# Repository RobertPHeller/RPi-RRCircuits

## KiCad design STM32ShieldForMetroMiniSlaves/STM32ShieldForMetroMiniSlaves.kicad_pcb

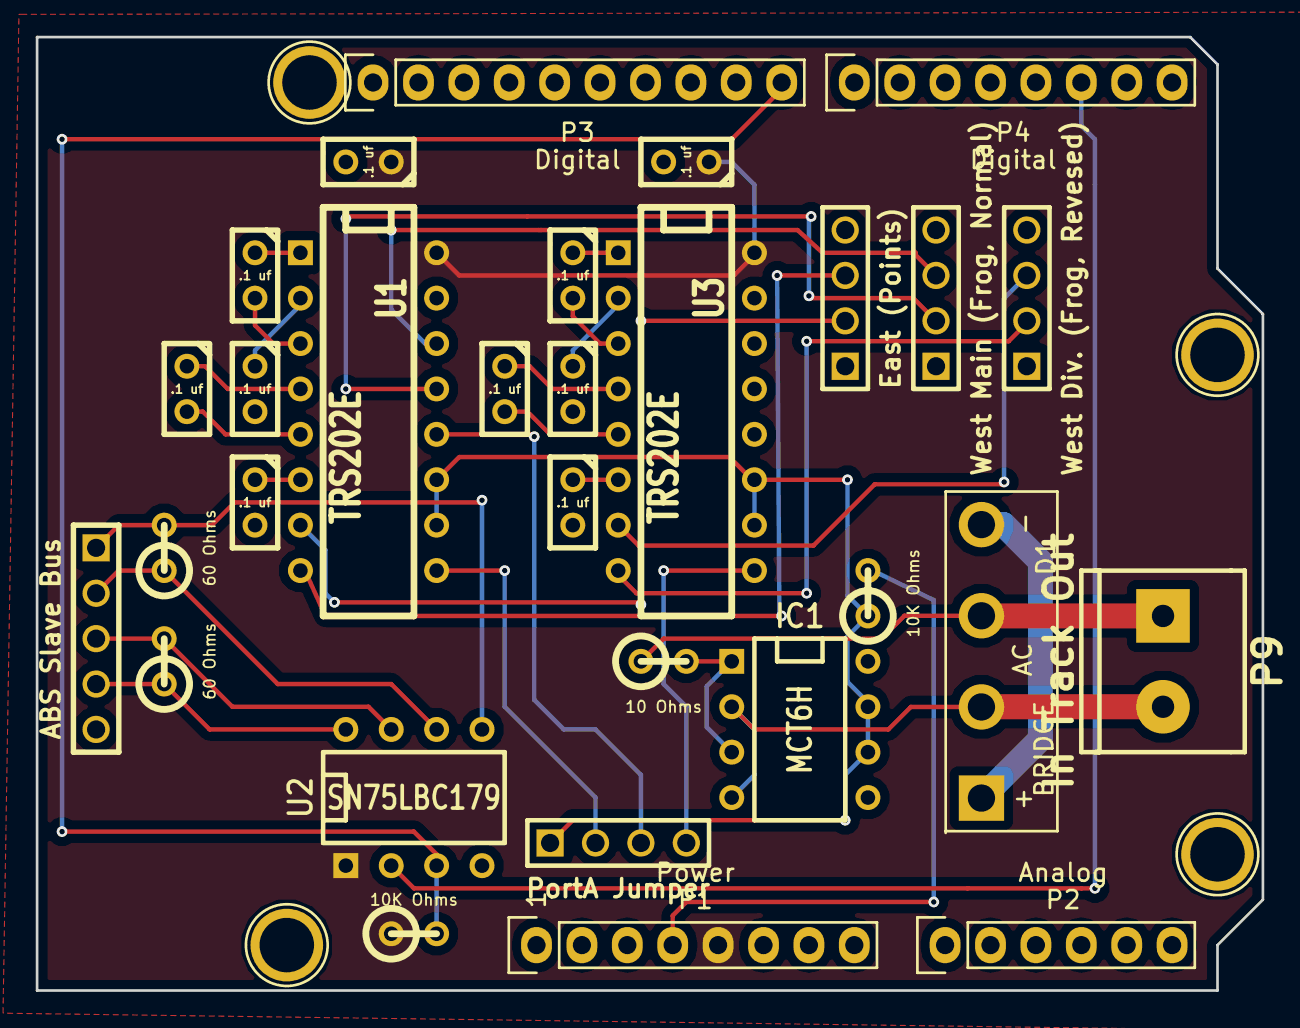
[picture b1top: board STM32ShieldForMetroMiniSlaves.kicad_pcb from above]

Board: 2 copper layers, 68.6 x 53.3 mm, 34 parts (0 on the bottom side), 35 nets.

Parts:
C1, C2, C3, C4, C5, C6, C7, C8, C9, C10: .1 uf; C1
D1: BRIDGE; KBL
IC1: MCT6H; DIP-8__300
P1: Power; Socket_Strip_Arduino_1x08
P2: Analog; Socket_Strip_Arduino_1x06
P3: Digital; Socket_Strip_Arduino_1x10
P4: Digital; Socket_Strip_Arduino_1x08
P5, P6, P7, P8: CONN_01X01; Arduino_1pin
P9: In Track Out; mors_2p
P10: East (Points); PIN_ARRAY_4x1
P11: West Main (Frog, Normal); PIN_ARRAY_4x1
P12: ABS Slave Bus; PIN_ARRAY_5x1
P13: West Div. (Frog, Revesed); PIN_ARRAY_4x1
P14: PortA Jumper; PIN_ARRAY_4x1
R1: 10 Ohms; R1
R2, R5: 10K Ohms; R1
R3, R4: 60 Ohms; R1
U1, U3: TRS202E; DIP-16__300
U2: SN75LBC179; DIP-8__300

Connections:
+3.3V: P1.4, R2.2
+5V: C5.1, C10.1, P1.5, R5.1, U1.16, U2.1, U3.16
/2: P4.6, U2.2
/8: P3.10, R5.2, U2.3
/PortA 5: IC1.6, IC1.7, P14.1, R2.1, U1.10, U1.11, U3.10, U3.11
/PortA 6: P14.2, U1.9
/PortA 7: P14.3, U1.12
/PortA 8: P14.4, U3.9
GND: C2.2, C4.2, C5.2, C7.2, C9.2, C10.2, IC1.5, IC1.8, P1.6, P1.7, P3.4, P10.1, P10.4, P11.1, P11.4, P12.5, P13.1, P13.4, U1.15, U2.4, U3.15
unnamed: D1.3, P9.1, R1.1
unnamed: D1.1, D1.4
unnamed: C3.1, U1.4
unnamed: C1.1, U1.1
unnamed: C4.1, U1.6
unnamed: D1.2, IC1.2, IC1.4, P9.2
unnamed: IC1.1, IC1.3, R1.2
unnamed: C3.2, U1.5
unnamed: C2.1, U1.2
unnamed: C1.2, U1.3
unnamed: P12.1, R3.2, U2.5
unnamed: P12.2, R3.1, U2.6
unnamed: P12.3, R4.2, U2.7
unnamed: P12.4, R4.1, U2.8
unnamed: P13.2, U3.8
unnamed: P11.2, U1.13
unnamed: P10.3, U1.8
unnamed: P13.3, U3.7
unnamed: P11.3, U1.14
unnamed: P10.2, U1.7
unnamed: C8.1, U3.4
unnamed: C6.1, U3.1
unnamed: C9.1, U3.6
unnamed: C8.2, U3.5
unnamed: C7.1, U3.2
unnamed: C6.2, U3.3

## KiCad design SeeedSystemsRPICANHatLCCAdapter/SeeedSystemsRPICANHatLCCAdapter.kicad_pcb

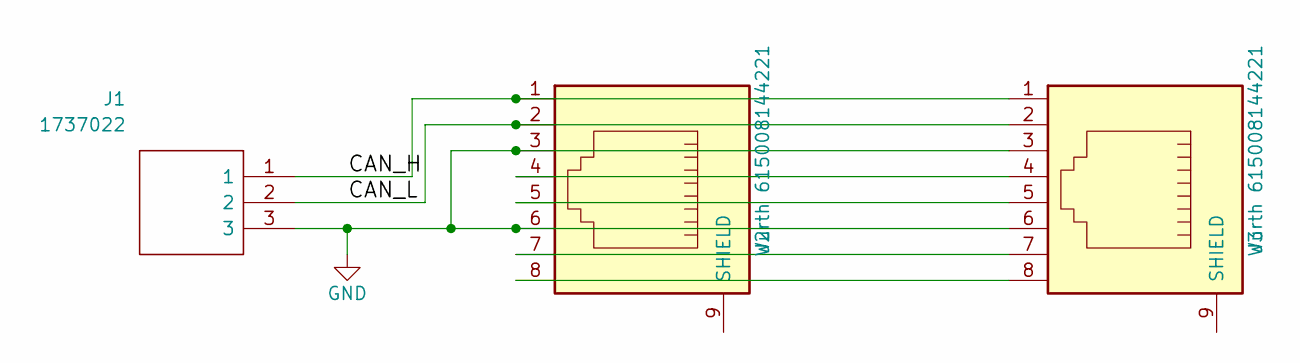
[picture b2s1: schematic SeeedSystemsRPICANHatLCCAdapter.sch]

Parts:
J1: 1737022; HDRRA3W100P0X350_1X3_1050X200X280P; Mouser Part Number 651-1737022
J2, J3: Wurth 615008144221; RJ45_8; Mouser Part Number 710-615008144221

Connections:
/CAN_H: J1.1, J2.1, J3.1
/CAN_L: J1.2, J2.2, J3.2
GND: J1.3, J2.3, J2.6, J3.3, J3.6
unnamed: J2.4, J3.4
unnamed: J2.5, J3.5
unnamed: J2.7, J3.7
unnamed: J2.8, J3.8

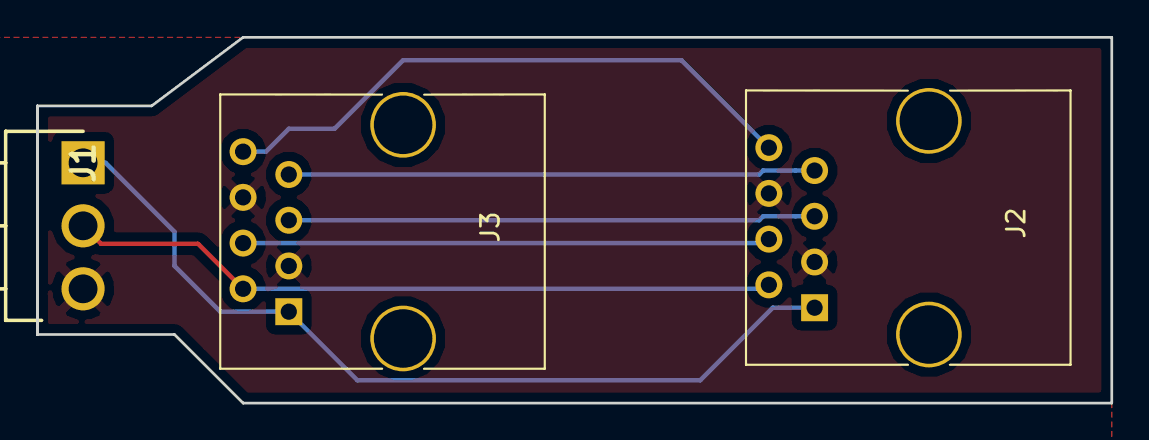
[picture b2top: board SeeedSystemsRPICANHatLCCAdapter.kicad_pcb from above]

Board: 2 copper layers, 59.7 x 20.3 mm, 3 parts (0 on the bottom side), 7 nets.

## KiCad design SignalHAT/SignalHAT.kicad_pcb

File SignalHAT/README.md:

# SignalHAT

This is a hat containing a MAX7221 driven off level shifted SPI.  It can 
drive up to 8 common-cathode signals of up to 8 LEDs each.

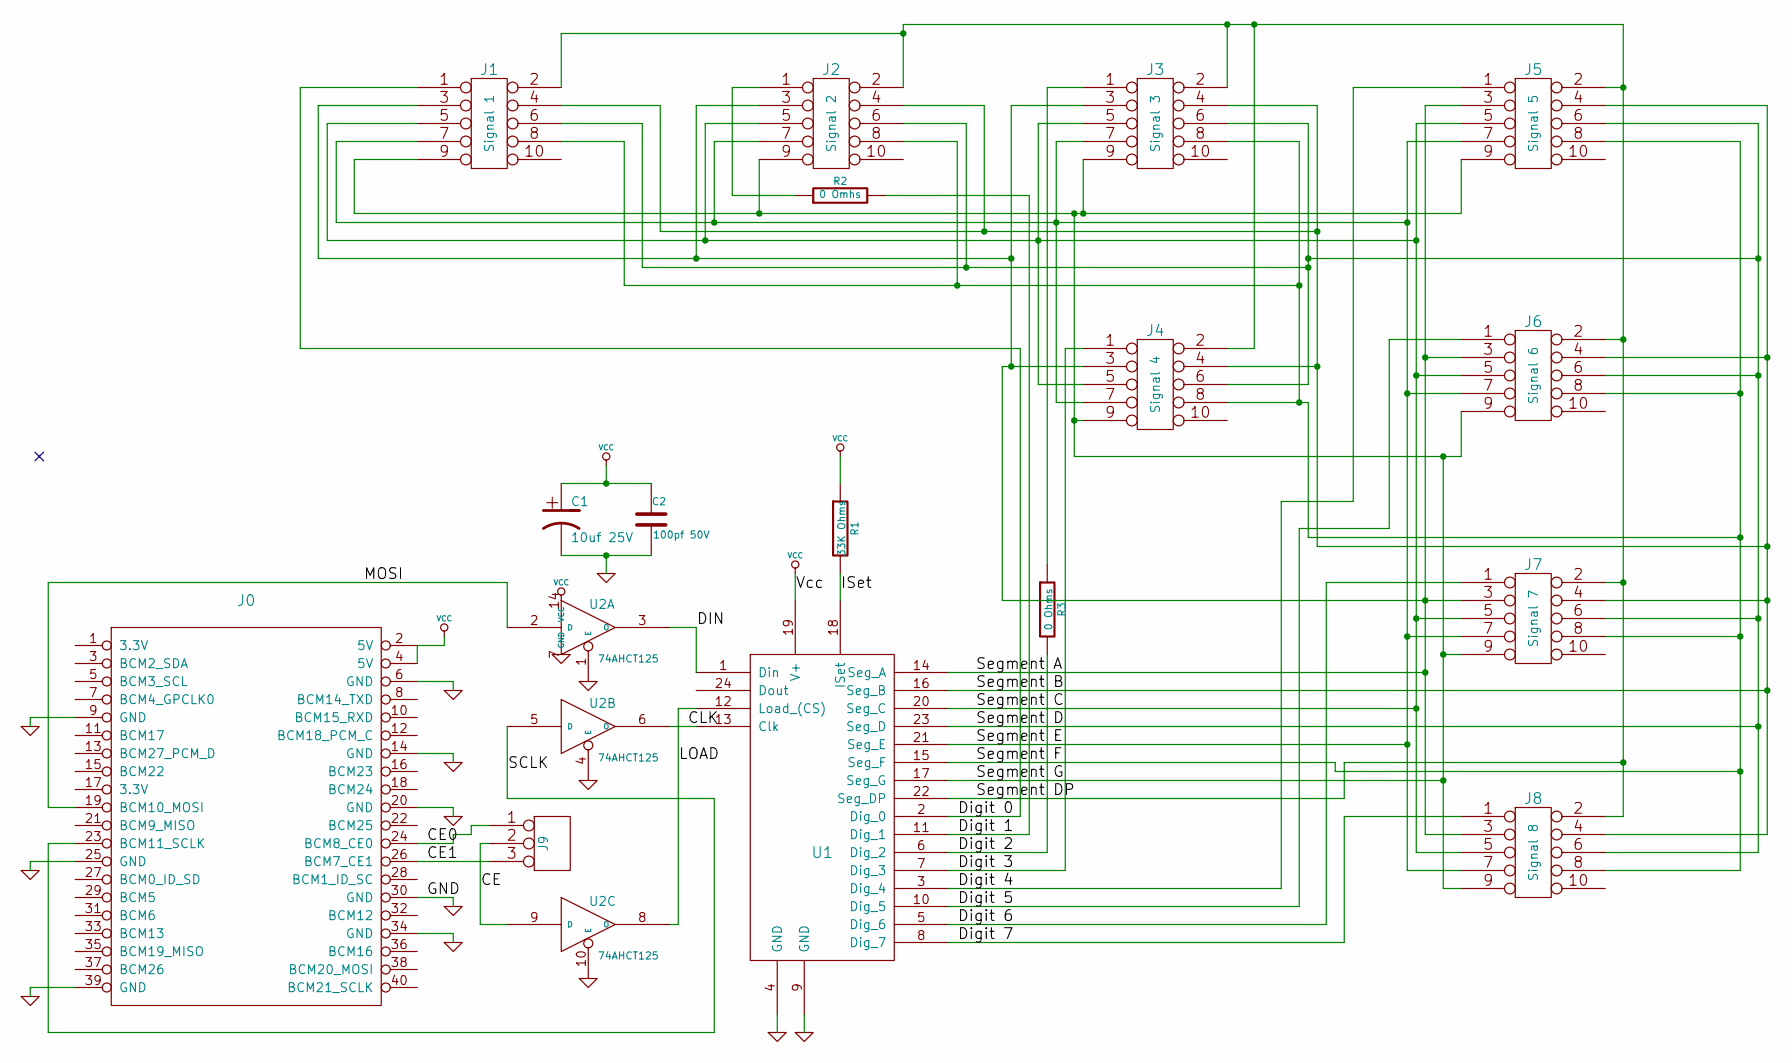
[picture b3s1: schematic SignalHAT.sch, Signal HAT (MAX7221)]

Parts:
C1: 10uf 25V; C1V5; Mouser Part Number 598-SK100M025ST
C2: 100pf 50V; C1; Mouser Part Number TAP104M035DCS
J0: RPi_GPIO; Pin_Header_Straight_2x20; Mouser Part Number 855-M20-6102045
J1: Signal 1; PIN_ARRAY_5x2; Mouser Part Number 538-70246-1001
J2: Signal 2; PIN_ARRAY_5x2; Mouser Part Number 538-70246-1001
J3: Signal 3; PIN_ARRAY_5x2; Mouser Part Number 538-70246-1001
J4: Signal 4; PIN_ARRAY_5x2; Mouser Part Number 538-70246-1001
J5: Signal 5; PIN_ARRAY_5x2; Mouser Part Number 538-70246-1001
J6: Signal 6; PIN_ARRAY_5x2; Mouser Part Number 538-70246-1001
J7: Signal 7; PIN_ARRAY_5x2; Mouser Part Number 538-70246-1001
J8: Signal 8; PIN_ARRAY_5x2; Mouser Part Number 538-70246-1001
J9: SIL 3 header; PIN_ARRAY_3X1; Mouser Part Number 538-22-28-8034
R1: 33K Ohms; R1; Mouser Part Number 660-MF1/4LCT52R333G
R2: 0 Omhs
R3: 0 Ohms
U1: MAX7221; DIP-24__300; Mouser Part Number 700-MAX7221CNG
U2: 74AHCT125; DIP-14__300; Mouser Part Number 595-SN74AHCT125N

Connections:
/CE: J9.2 (PM), U2.9 (D)
/CE0: J0.24 (BCM8_CE0), J9.1
/CE1: J0.26 (BCM7_CE1), J9.3
/CLK: U1.13 (Clk), U2.6 (O)
/DIN: U1.1 (Din), U2.3 (O)
/Digit 0: J1.1, U1.2 (Dig_0)
/Digit 1: R2.2, U1.11 (Dig_1)
/Digit 2: R3.2, U1.6 (Dig_2)
/Digit 3: J4.1, U1.7 (Dig_3)
/Digit 4: J5.1, U1.3 (Dig_4)
/Digit 5: J6.1, U1.10 (Dig_5)
/Digit 6: J7.1, U1.5 (Dig_6)
/Digit 7: J8.1, U1.8 (Dig_7)
/ISet: R1.2, U1.18 (ISet)
/LOAD: U1.12 (Load_(CS)), U2.8 (O)
/MOSI: J0.19 (BCM10_MOSI), U2.2 (D)
/SCLK: J0.23 (BCM11_SCLK), U2.5 (D)
/Segment A: J1.3, J2.3, J3.3, J4.3, J5.3, J6.3, J7.3, J8.3, U1.14 (Seg_A)
/Segment B: J1.4, J2.4, J3.4, J4.4, J5.4, J6.4, J7.4, J8.4, U1.16 (Seg_B)
/Segment C: J1.5, J2.5, J3.5, J4.5, J5.5, J6.5, J7.5, J8.5, U1.20 (Seg_C)
/Segment D: J1.6, J2.6, J3.6, J4.6, J5.6, J6.6, J7.6, J8.6, U1.23 (Seg_D)
/Segment DP: J1.2, J2.2, J3.2, J4.2, J5.2, J6.2, J7.2, J8.2, U1.22 (Seg_DP)
/Segment E: J1.7, J2.7, J3.7, J4.7, J5.7, J6.7, J7.7, J8.7, U1.21 (Seg_E)
/Segment F: J1.8, J2.8, J3.8, J4.8, J5.8, J6.8, J7.8, J8.8, U1.15 (Seg_F)
/Segment G: J1.9, J2.9, J3.9, J4.9, J5.9, J6.9, J7.9, J8.9, U1.17 (Seg_G)
GND: C1.2, C2.2, J0.6 (GND), J0.9 (GND), J0.14 (GND), J0.20 (GND), J0.25 (GND), J0.30 (GND), J0.34 (GND), J0.39 (GND), U1.4 (GND), U1.9 (GND), U2.1 (E), U2.4 (E), U2.7 (GND), U2.10 (E)
unnamed: J2.1, R2.1
unnamed: J3.1, R3.1
VCC: C1.1, C2.1, J0.2 (5V), J0.4 (5V), R1.1, U1.19 (V+), U2.14 (VCC)

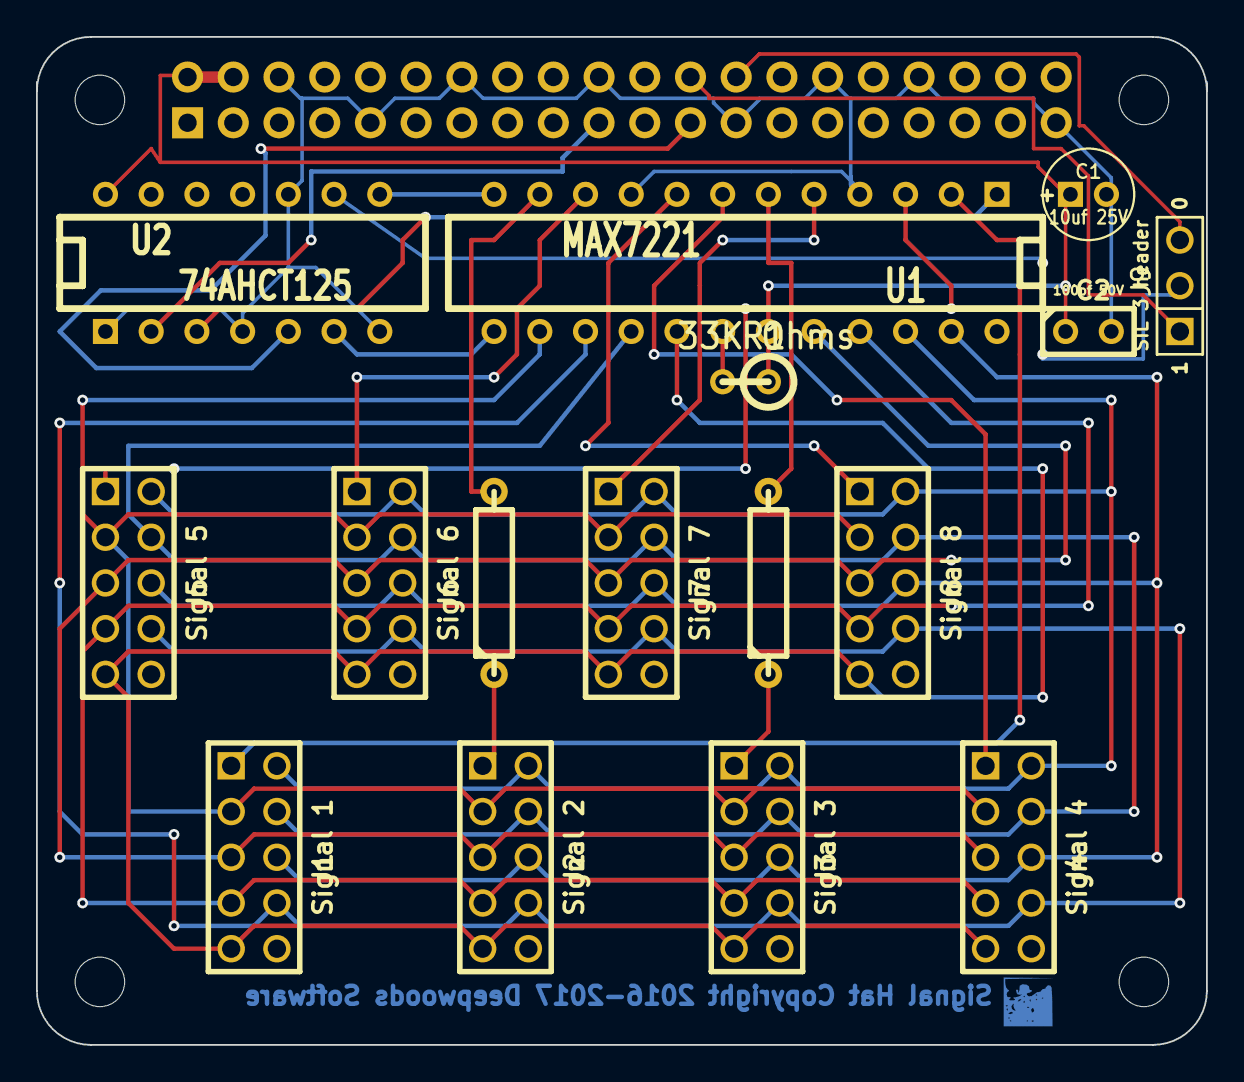
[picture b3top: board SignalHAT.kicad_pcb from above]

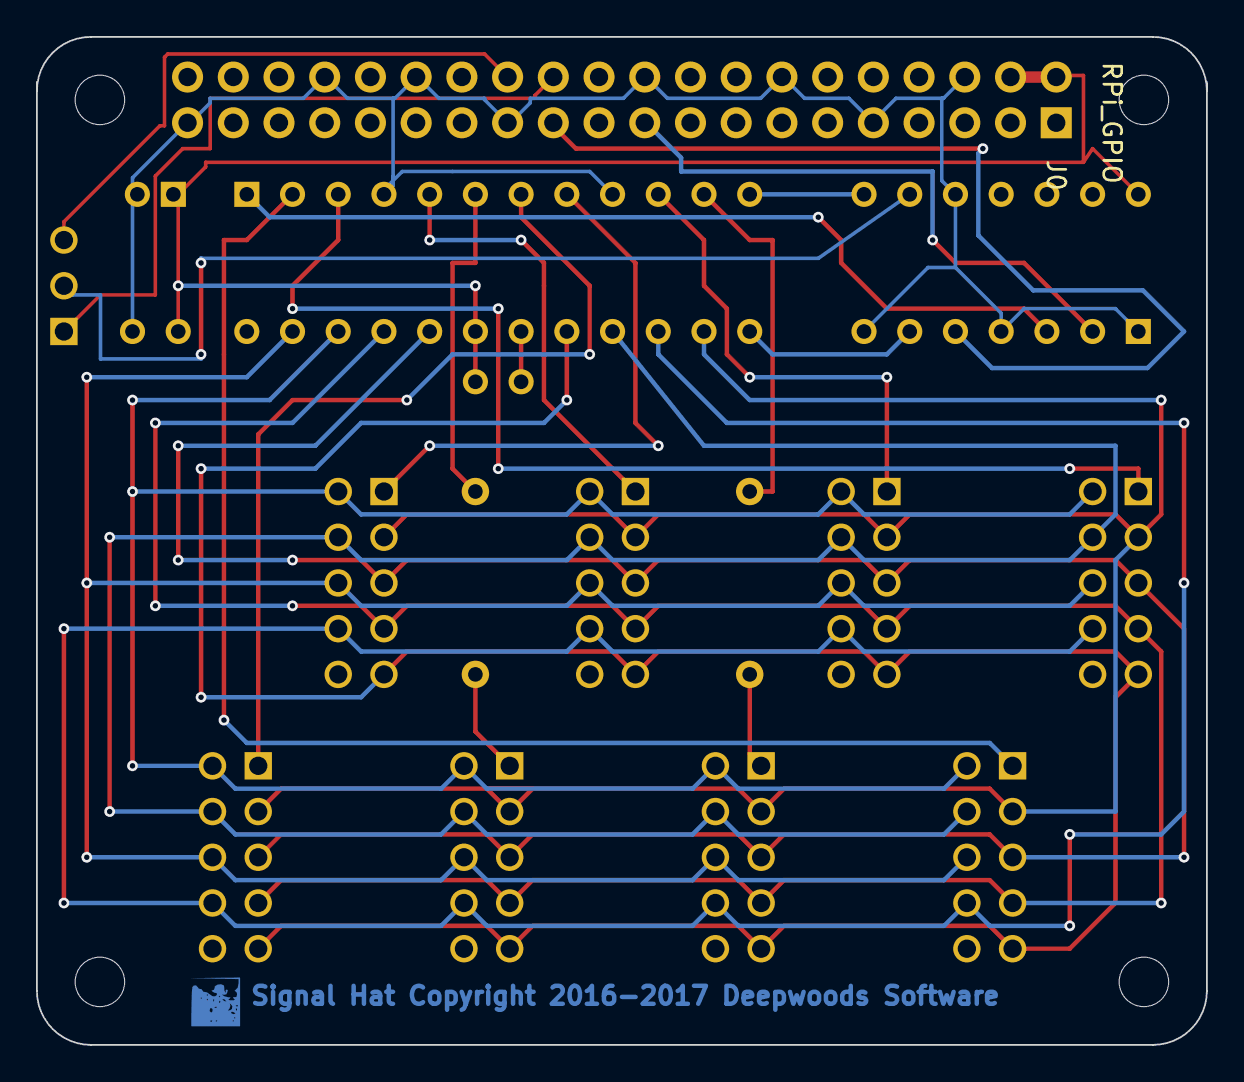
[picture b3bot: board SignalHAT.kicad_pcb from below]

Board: 2 copper layers, 65.0 x 56.0 mm, 21 parts (5 on the bottom side), 29 nets.

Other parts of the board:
H1, H2, H3, H4: RPi_Hat_Mounting_Hole

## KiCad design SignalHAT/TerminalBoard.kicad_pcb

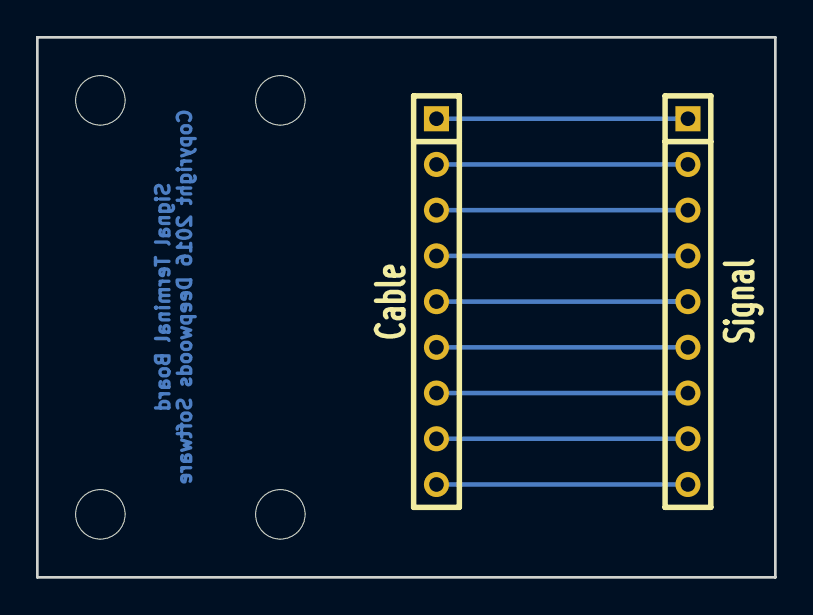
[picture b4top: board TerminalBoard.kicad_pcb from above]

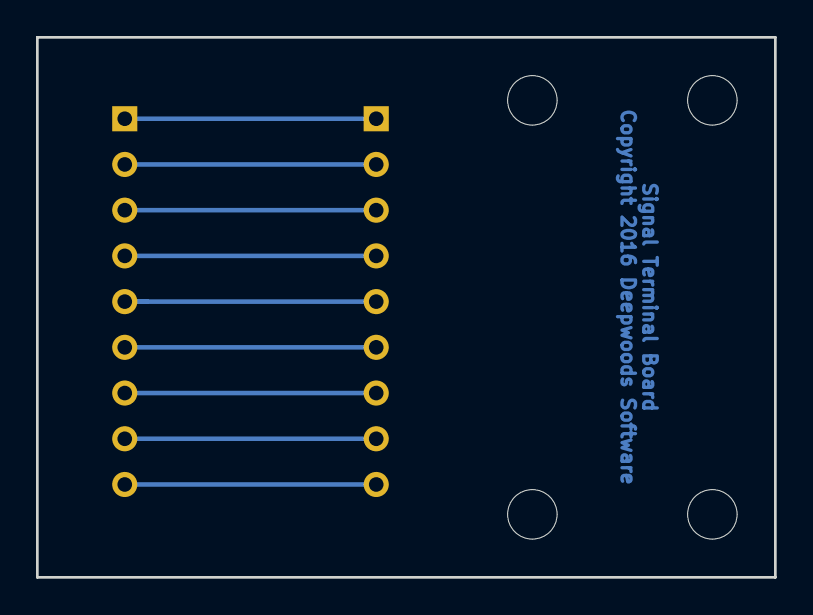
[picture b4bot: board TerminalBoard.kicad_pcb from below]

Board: 2 copper layers, 41.0 x 30.0 mm, 6 parts (4 on the bottom side), 9 nets.

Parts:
H1, H2, H3, H4: RPi_Hat_Mounting_Hole
SIL-9: Signal; SIL-9
T0: Cable; SIL-9

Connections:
/Digit Common: SIL-9.1, T0.1
/Segment A: SIL-9.3, T0.3
/Segment B: SIL-9.4, T0.4
/Segment C: SIL-9.5, T0.5
/Segment D: SIL-9.6, T0.6
/Segment DP: SIL-9.2, T0.2
/Segment E: SIL-9.7, T0.7
/Segment F: SIL-9.8, T0.8
/Segment G: SIL-9.9, T0.9

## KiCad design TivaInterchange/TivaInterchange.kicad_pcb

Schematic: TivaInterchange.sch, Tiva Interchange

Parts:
J1: TI_BOOSTER_40_J1
J2: TI_BOOSTER_40_J2
J3: TI_BOOSTER_40_J3
J4: TI_BOOSTER_40_J4
P3: CONN_10

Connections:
+3.3V: J1.1; also elsewhere on the board
/QuadSignalHead/SCL: J1.9; also elsewhere on the board
/QuadSignalHead/SDA: J1.10; also elsewhere on the board
/SMCSense/Motor Select 1: J3.3; also elsewhere on the board
/SMCSense/Motor Select 2: J3.4; also elsewhere on the board
/SMCSense/Point Sense 1: J3.5; also elsewhere on the board
/SMCSense/Point Sense 2: J3.6; also elsewhere on the board
Common: J3.1, P3.5; also elsewhere on the board
GND: J2.1, J3.2, P3.6; also elsewhere on the board
unnamed: J3.8, P3.2
unnamed: J3.7, P3.1
unnamed: J4.7, P3.7
unnamed: J4.8, P3.8
unnamed: J4.9, P3.9
unnamed: J4.10, P3.10
unnamed: J3.10, P3.4
unnamed: J3.9, P3.3

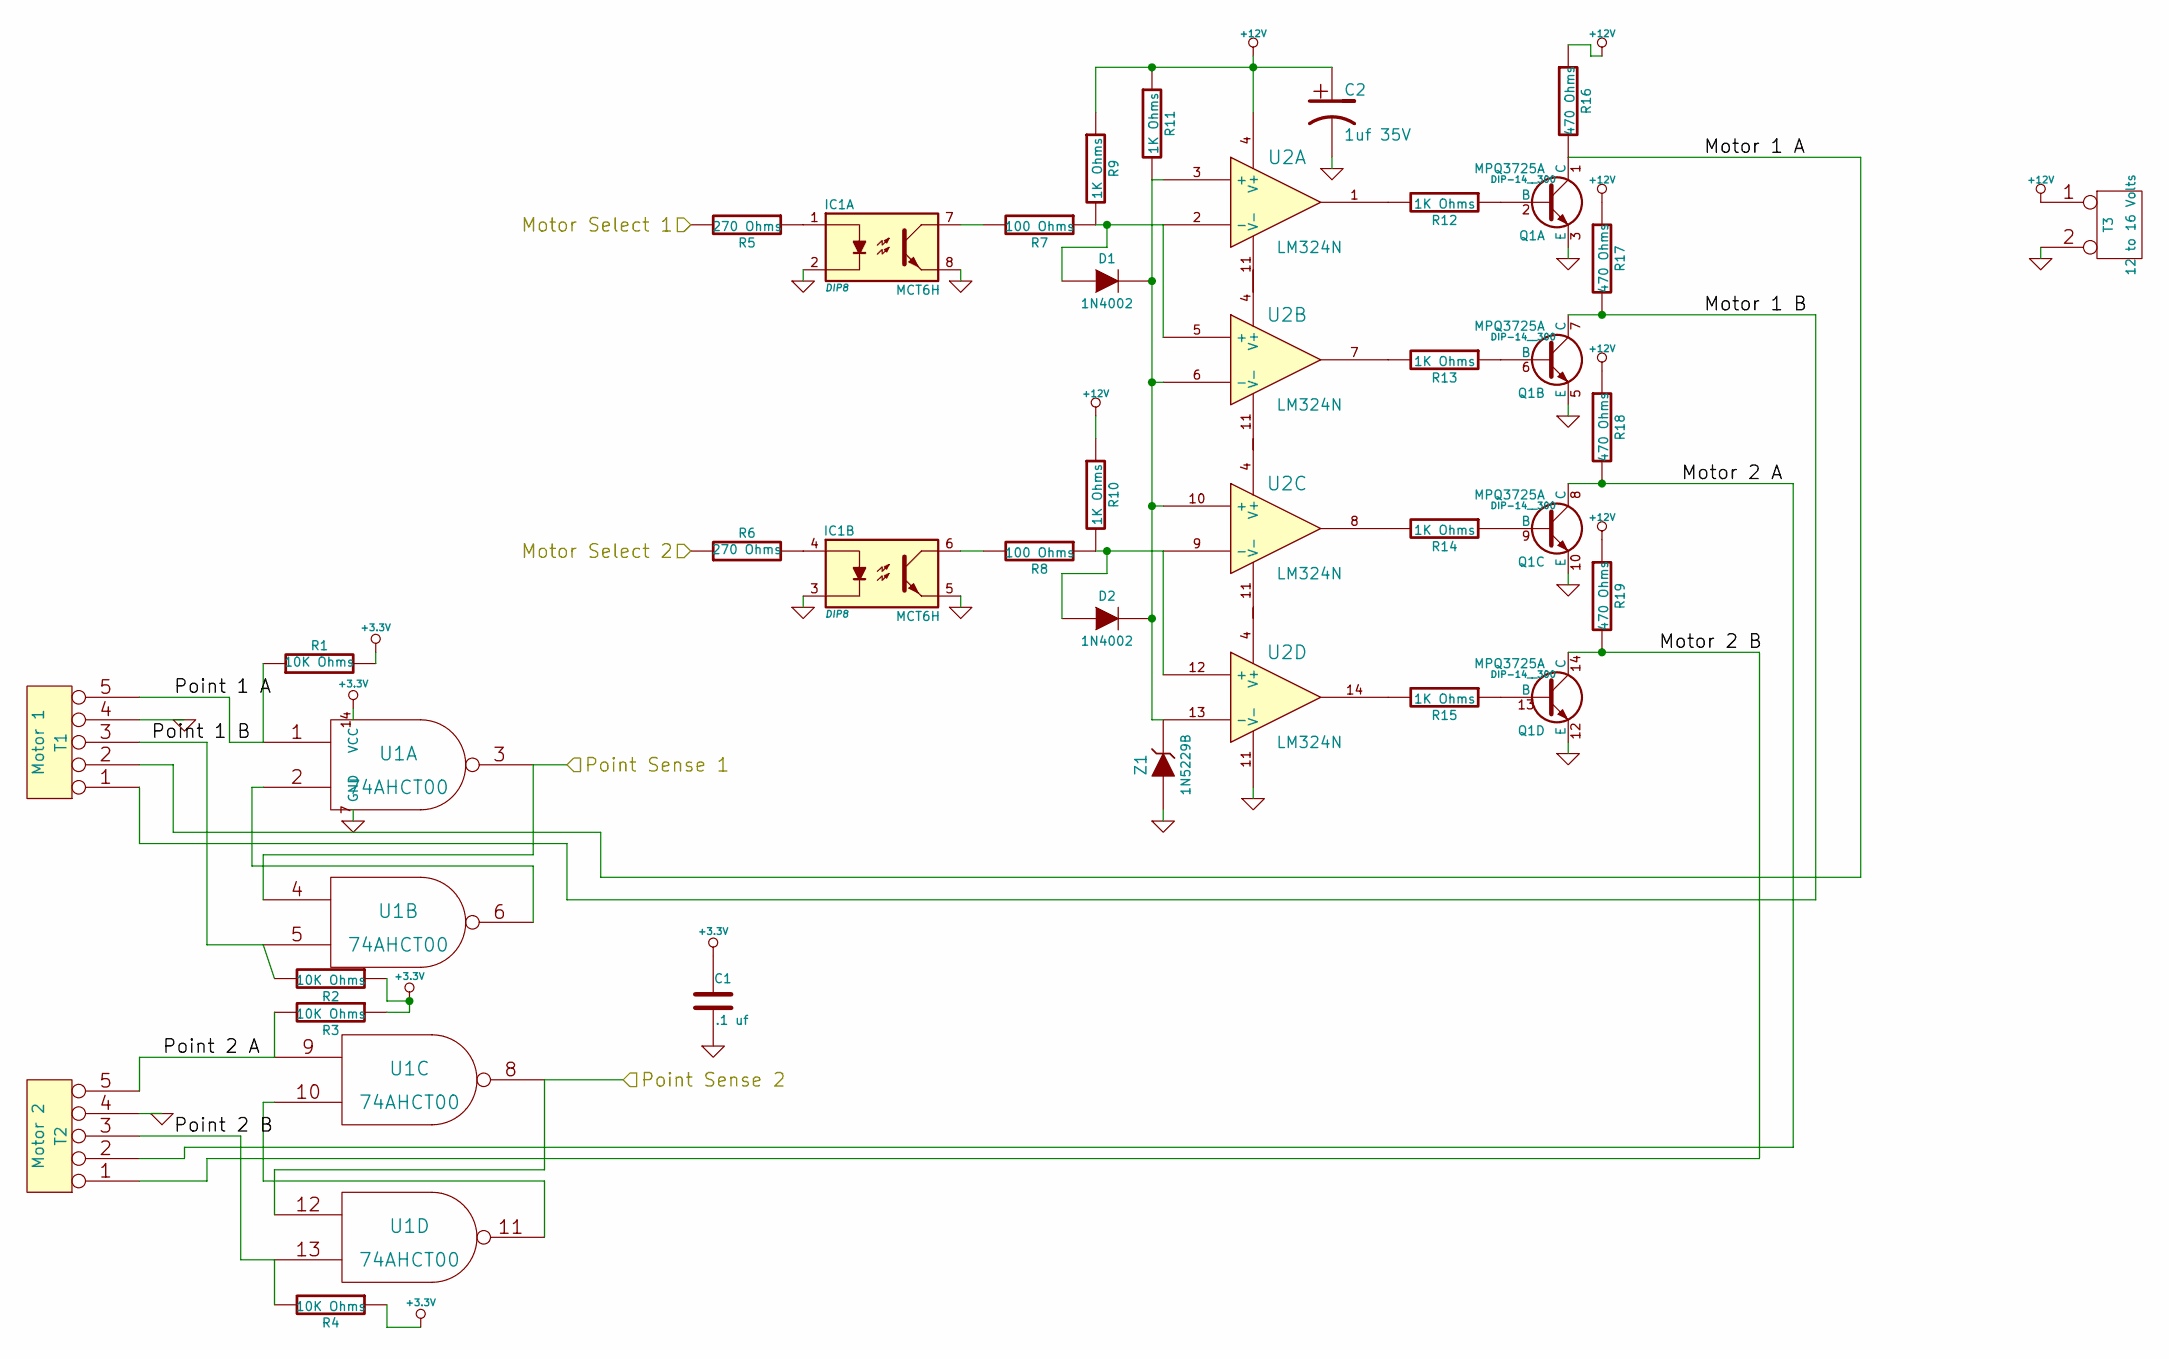
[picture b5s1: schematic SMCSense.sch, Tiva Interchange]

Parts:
C1: .1 uf; Mouser part Number 21RZ310-RC
C2: 1uf 35V; Mouser Part Number 74-199D105X9035A1VE3
D1, D2: 1N4002; Mouser Part Number 833-1N4002-TP
IC1: MCT6H; DIP8; Mouser part Number 782-MCT6H
Q1: MPQ3725A; DIP-14__300; Mouser part Number 610-MPQ3725A
R1, R2, R3, R4: 10K Ohms; Mouser Part Number 603-CFR-25JR-5210K
R5, R6: 270 Ohms; Mouser Part Number 603-CFR-25JR-52-270R
R7, R8: 100 Ohms; Mouser Part Number 603-CFR-25JR-52100R
R9: 1K Ohms; Mouser part Number 279-2-1623927-3
R10, R11, R12, R13, R14, R15: 1K Ohms; Mouser Part Number 279-2-1623927-3
R16: 470 Ohms; Mouser part Number 279-CFR50J470R
R17, R18: 470 Ohms; Mouser Part Number 279-CFR50J470R
R19: 470 Ohms; Mousere Part Number 279-CFR50J470R
T1: Motor 1; Mouser Part Number 571-282834-5
T2: Motor 2; Mouser Part Number 571-282834-5
T3: 12 to 16 Volts; Mouser Partnumber 571-282834-2
U1: 74AHCT00; Mouser part Number 595-SN74AHC00N
U2: LM324N; Mouser part Number 512-LM324N
Z1: 1N5229B; Mouser Part Number 512-1N5229BTR

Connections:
+3.3V: C1.1, R1.2, R2.1, R3.1, R4.1, U1.14 (VCC); also elsewhere on the board
+12V: C2.1, R9.1, R10.1, R11.1, R16.1, R17.1, R18.1, R19.1, T3.1, U2.4 (V+)
/SMCSense/Motor 1 A: Q1.1 (C), R16.2, T1.2
/SMCSense/Motor 1 B: Q1.7 (C), R17.2, T1.1
/SMCSense/Motor 2 A: Q1.8 (C), R18.2, T2.2
/SMCSense/Motor 2 B: Q1.14 (C), R19.2, T2.1
/SMCSense/Motor Select 1: R5.2; also elsewhere on the board
/SMCSense/Motor Select 2: R6.1; also elsewhere on the board
/SMCSense/Point 1 A: R1.1, T1.5, U1.1
/SMCSense/Point 1 B: R2.2, T1.3, U1.5
/SMCSense/Point 2 A: R3.2, T2.5, U1.9
/SMCSense/Point 2 B: R4.2, T2.3, U1.13
/SMCSense/Point Sense 1: U1.3, U1.4; also elsewhere on the board
/SMCSense/Point Sense 2: U1.8, U1.12; also elsewhere on the board
GND: C1.2, C2.2, IC1.2, IC1.3, IC1.5, IC1.8, Q1.3 (E), Q1.5 (E), Q1.10 (E), Q1.12 (E), T1.4, T2.4, T3.2 (PM), U1.7 (GND), U2.11 (V-), Z1.1 (A); also elsewhere on the board
unnamed: R15.2, U2.14
unnamed: Q1.13 (B), R15.1
unnamed: Q1.9 (B), R14.1
unnamed: Q1.6 (B), R13.1
unnamed: Q1.2 (B), R12.1
unnamed: R12.2, U2.1
unnamed: R13.2, U2.7
unnamed: R14.2, U2.8
unnamed: IC1.6, R8.2
unnamed: D2.1 (A), R8.1, R10.2, U2.9 (-), U2.12 (+)
unnamed: IC1.4, R6.2
unnamed: IC1.1, R5.1
unnamed: U1.2, U1.6
unnamed: IC1.7, R7.2
unnamed: U1.10, U1.11
unnamed: D1.1 (A), R7.1, R9.2, U2.2 (-), U2.5 (+)
unnamed: D1.2 (K), D2.2 (K), R11.2, U2.3 (+), U2.6 (-), U2.10 (+), U2.13 (-), Z1.2 (K)

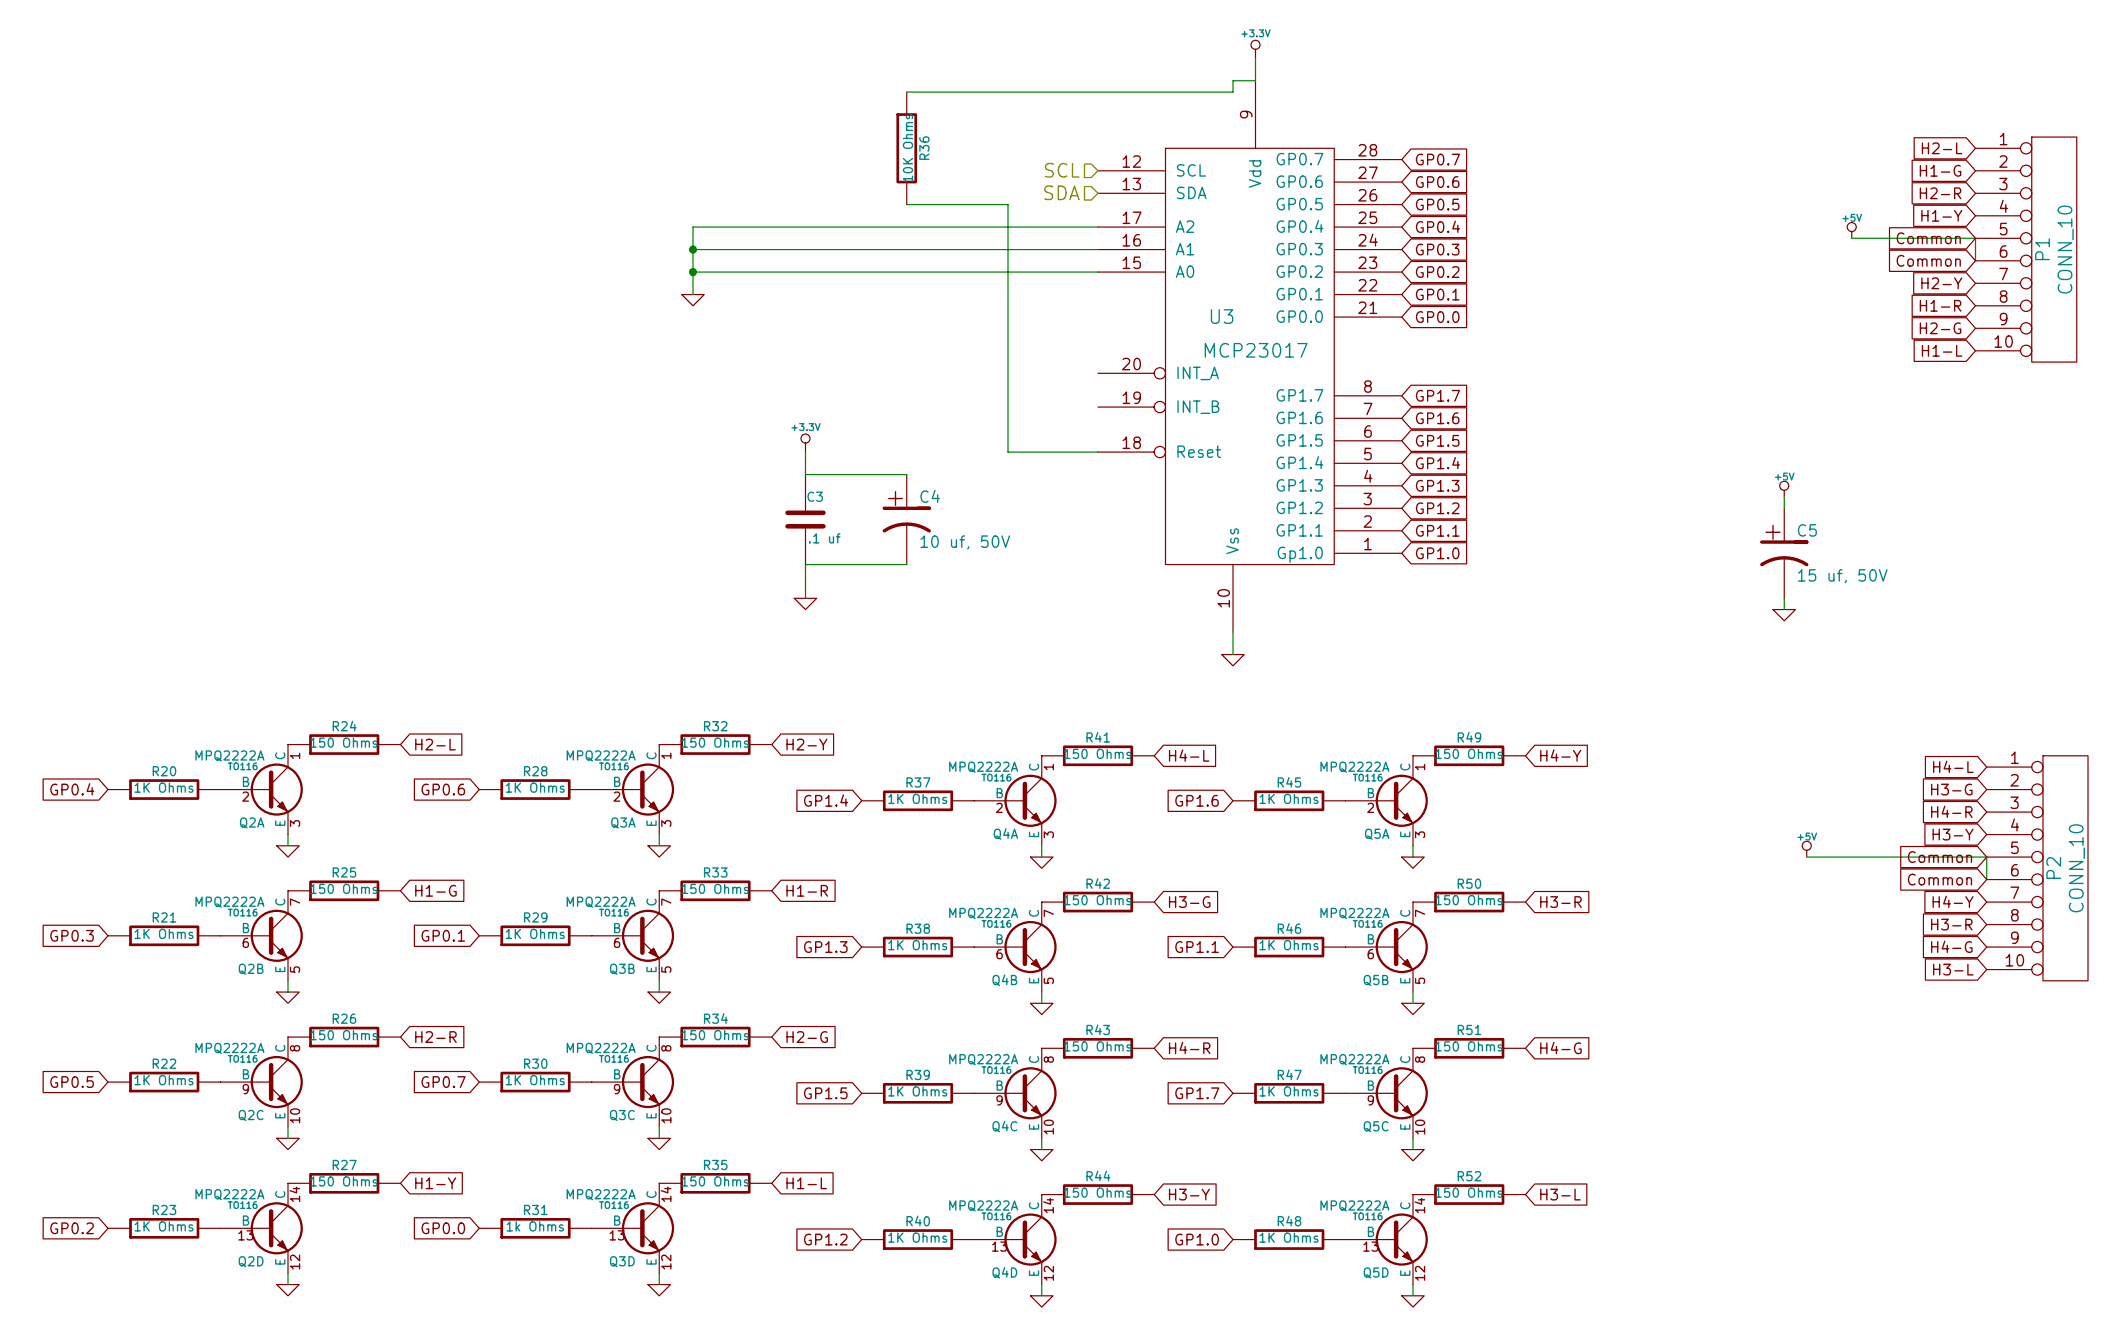
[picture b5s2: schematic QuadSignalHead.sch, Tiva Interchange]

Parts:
C3: .1 uf
C4: 10 uf, 50V
C5: 15 uf, 50V
P1, P2: CONN_10
Q2, Q3, Q4, Q5: MPQ2222A; TO116
R20, R21, R22, R23, R28, R29, R30, R37, R38, R39, R40, R45, R46, R47, R48: 1K Ohms
R24, R25, R26, R27, R32, R33, R34, R35, R41, R42, R43, R44, R49, R50, R51, R52: 150 Ohms
R31: 1k Ohms
R36: 10K Ohms
U3: MCP23017

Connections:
+3.3V: C3.1, C4.1, R36.1, U3.9 (Vdd); also elsewhere on the board
/QuadSignalHead/SCL: U3.12 (SCL); also elsewhere on the board
/QuadSignalHead/SDA: U3.13 (SDA); also elsewhere on the board
Common: C5.1, P1.5, P1.6, P2.5, P2.6; also elsewhere on the board
GND: C3.2, C4.2, C5.2, Q2.3 (E), Q2.5 (E), Q2.10 (E), Q2.12 (E), Q3.3 (E), Q3.5 (E), Q3.10 (E), Q3.12 (E), Q4.3 (E), Q4.5 (E), Q4.10 (E), Q4.12 (E), Q5.3 (E), Q5.5 (E), Q5.10 (E), Q5.12 (E), U3.10 (Vss), U3.15 (A0), U3.16 (A1), U3.17 (A2); also elsewhere on the board
GP0.0: R31.1, U3.21 (GP0.0)
GP0.1: R29.1, U3.22 (GP0.1)
GP0.2: R23.1, U3.23 (GP0.2)
GP0.3: R21.1, U3.24 (GP0.3)
GP0.4: R20.1, U3.25 (GP0.4)
GP0.5: R22.1, U3.26 (GP0.5)
GP0.6: R28.1, U3.27 (GP0.6)
GP0.7: R30.1, U3.28 (GP0.7)
GP1.0: R48.1, U3.1 (Gp1.0)
GP1.1: R46.1, U3.2 (GP1.1)
GP1.2: R40.1, U3.3 (GP1.2)
GP1.3: R38.1, U3.4 (GP1.3)
GP1.4: R37.1, U3.5 (GP1.4)
GP1.5: R39.1, U3.6 (GP1.5)
GP1.6: R45.1, U3.7 (GP1.6)
GP1.7: R47.1, U3.8 (GP1.7)
H1-G: P1.2, R25.2
H1-L: P1.10, R35.2
H1-R: P1.8, R33.2
H1-Y: P1.4, R27.2
H2-G: P1.9, R34.2
H2-L: P1.1, R24.2
H2-R: P1.3, R26.2
H2-Y: P1.7, R32.2
H3-G: P2.2, R42.2
H3-L: P2.10, R52.2
H3-R: P2.8, R50.2
H3-Y: P2.4, R44.2
H4-G: P2.9, R51.2
H4-L: P2.1, R41.2
H4-R: P2.3, R43.2
H4-Y: P2.7, R49.2
unnamed: Q5.14 (C), R52.1
unnamed: Q5.13 (B), R48.2
unnamed: R36.2, U3.18 (Reset)
unnamed: Q2.14 (C), R27.1
unnamed: Q2.13 (B), R23.2
unnamed: Q2.8 (C), R26.1
unnamed: Q2.9 (B), R22.2
unnamed: Q3.8 (C), R34.1
unnamed: Q3.7 (C), R33.1
unnamed: Q3.6 (B), R29.2
unnamed: Q3.1 (C), R32.1
unnamed: Q3.2 (B), R28.2
unnamed: Q2.7 (C), R25.1
unnamed: Q2.6 (B), R21.2
unnamed: Q2.1 (C), R24.1
unnamed: Q2.2 (B), R20.2
unnamed: Q5.1 (C), R49.1
unnamed: Q5.2 (B), R45.2
unnamed: Q4.14 (C), R44.1
unnamed: Q4.13 (B), R40.2
unnamed: Q5.8 (C), R51.1
unnamed: Q5.9 (B), R47.2
unnamed: Q5.7 (C), R50.1
unnamed: Q5.6 (B), R46.2
unnamed: Q4.2 (B), R37.2
unnamed: Q4.1 (C), R41.1
unnamed: Q3.14 (C), R35.1
unnamed: Q3.13 (B), R31.2
unnamed: Q3.9 (B), R30.2
unnamed: Q4.8 (C), R43.1
unnamed: Q4.9 (B), R39.2
unnamed: Q4.7 (C), R42.1
unnamed: Q4.6 (B), R38.2

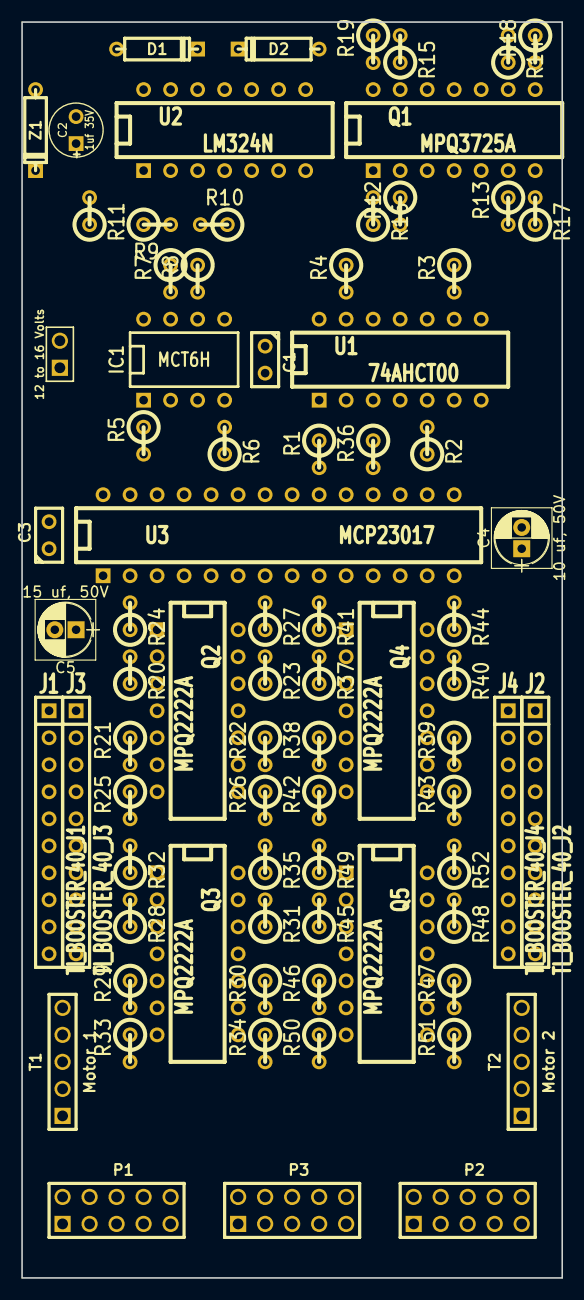
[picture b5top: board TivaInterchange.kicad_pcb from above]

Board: 2 copper layers, 50.8 x 118.1 mm, 79 parts (0 on the bottom side), 108 nets.

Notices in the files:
SignalHAT/SignalHAT.kicad_pcb:
Signal Hat Copyright 2016-2017 Deepwoods Software
SignalHAT/TerminalBoard.kicad_pcb:
Copyright 2016 Deepwoods Software
